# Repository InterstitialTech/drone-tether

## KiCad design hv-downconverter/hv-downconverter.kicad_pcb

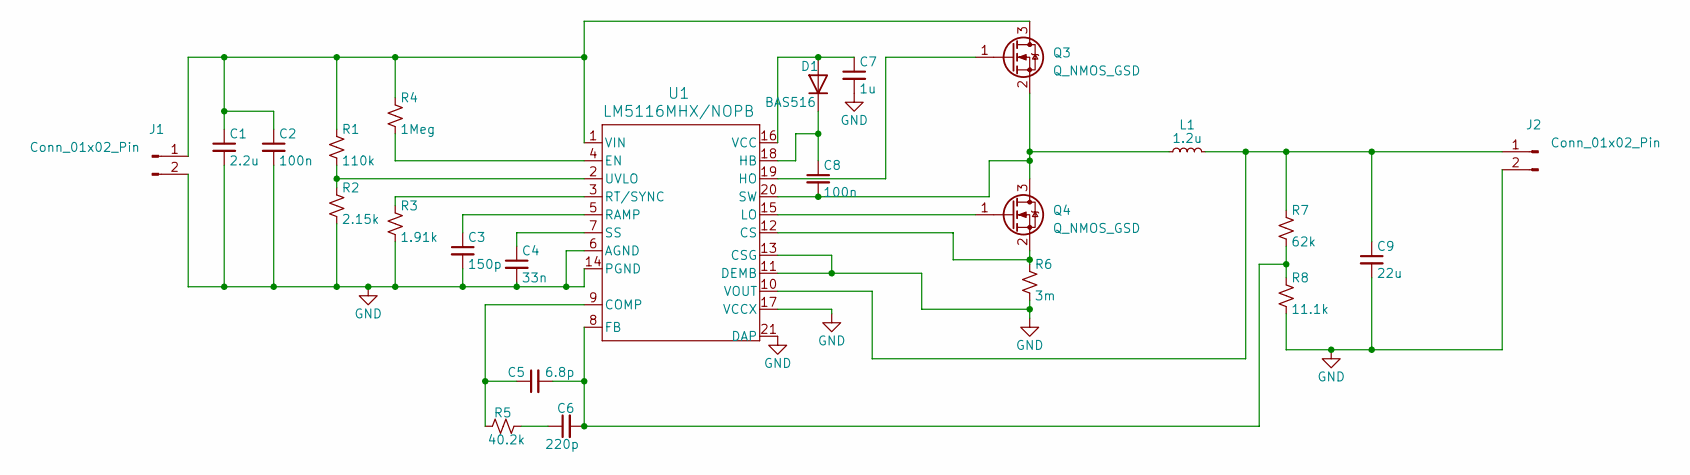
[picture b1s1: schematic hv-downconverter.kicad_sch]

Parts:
C1: 2.2u; C_1210_3225Metric
C2, C8: 100n; C_0603_1608Metric
C3: 150p; C_0603_1608Metric
C4: 33n; C_0603_1608Metric
C5: 6.8p; C_0603_1608Metric
C6: 220p; C_0603_1608Metric
C7: 1u; C_0805_2012Metric
C9: 22u; C_2220_5650Metric
D1: BAS516; D_SOD-523
J1, J2: Conn_01x02_Pin; PinHeader_1x02_P2.54mm_Vertical
L1: 1.2u; L_Coilcraft_XAL7070-XXX
Q3, Q4: Q_NMOS_GSD; PQFN_8x8
R1: 110k; R_0805_2012Metric
R2: 2.15k; R_0603_1608Metric
R3: 1.91k; R_0603_1608Metric
R4: 1Meg; R_0603_1608Metric
R5: 40.2k; R_0603_1608Metric
R6: 3m; R_1206_3216Metric
R7: 62k; R_0603_1608Metric
R8: 11.1k; R_0603_1608Metric
U1: LM5116MHX/NOPB; MXA20A_TEX

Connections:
GND: C1.2, C2.2, C3.2, C4.2, C7.2, C9.2, J1.2, J2.2, R2.2, R3.2, R6.2, R8.2, U1.6 (AGND), U1.11 (DEMB), U1.13 (CSG), U1.14 (PGND), U1.17 (VCCX), U1.21 (DAP)
unnamed: C6.1, R5.2
unnamed: C7.1, D1.2 (A), U1.16 (VCC)
unnamed: C8.1, D1.1 (K), U1.18 (HB)
unnamed: C1.1, C2.1, J1.1, Q3.3 (D), R1.1, R4.1, U1.1 (VIN)
unnamed: C9.1, J2.1, L1.2, R7.1, U1.10 (VOUT)
unnamed: Q3.1 (G), U1.19 (HO)
unnamed: C8.2, L1.1, Q3.2 (S), Q4.3 (D), U1.20 (SW)
unnamed: Q4.1 (G), U1.15 (LO)
unnamed: Q4.2 (S), R6.1, U1.12 (CS)
unnamed: C5.1, R5.1, U1.9 (COMP)
unnamed: R4.2, U1.4 (EN)
unnamed: C5.2, C6.2, R7.2, R8.1, U1.8 (FB)
unnamed: C3.1, U1.5 (RAMP)
unnamed: R3.1, U1.3 (RT/SYNC)
unnamed: C4.1, U1.7 (SS)
unnamed: R1.2, R2.1, U1.2 (UVLO)

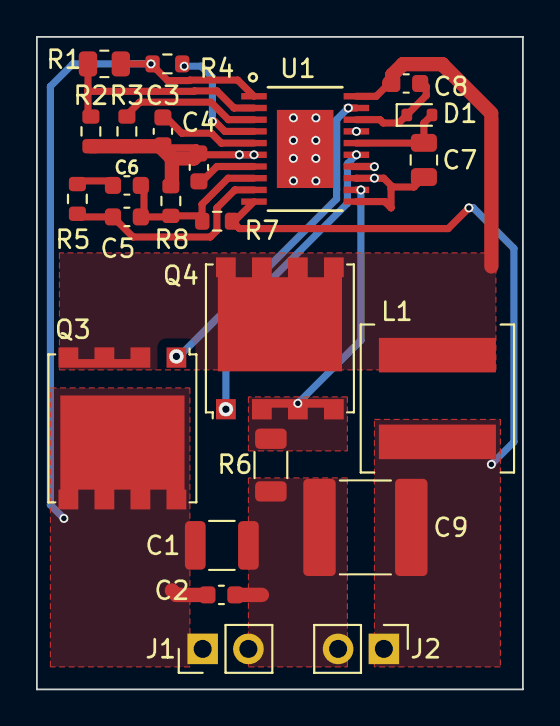
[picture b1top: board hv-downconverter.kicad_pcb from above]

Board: 4 copper layers, 27.0 x 36.2 mm, 24 parts (0 on the bottom side), 17 nets.

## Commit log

2024-09-04 its a start
2024-09-06 schematic captured, starting to place components
2024-09-10 almost ready for fab
2024-09-16 nearly at production
